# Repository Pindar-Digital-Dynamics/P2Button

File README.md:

# P2Button
The Pbutton project is designed to create a Bluetooth Low Energy (BLE) controlled video recording system specifically for Android platforms, primarily for indoor environments like gyms. This innovative system enables users to operate video recording functions through a robust, mounted button system, making it highly accessible and user-friendly.

## Overview
This project is a BLE (Bluetooth Low Energy) device setup for the P2CAM application, featuring a combination of functionalities including:
- BLE services and characteristics for communication.
- An OLED display for visual feedback.
- A buzzer and LEDs for status indication.
- Button interactions for triggering specific actions.

The code is designed to manage device states, interact with a BLE client, and provide visual/audio feedback for user interactions.

---

## Features
1. **BLE Communication**:
   - Implements multiple services and characteristics.
   - Supports read, write, indicate, and notify operations.
   - Handles commands like "Unlock", "Record", "Upload", "Login", and more.

2. **OLED Display**:
   - Displays the P2CAM logo, messages, and countdown timers.
   - Provides visual feedback during various states.

3. **Device States**:
   - The device transitions through states such as `NOT_PAIRED`, `LOGGED_LOCKED`, `CAMERA_UNLOCKED`, `RECORDING`, and more.

4. **LED Indications**:
   - Different LED colors indicate different device states.

5. **Buzzer Notifications**:
   - Provides audio feedback for specific actions.

6. **Button Interaction**:
   - Short and long press interactions trigger state changes and actions.

---

## Hardware Requirements
- **Microcontroller**: ESP32 or similar with BLE support.
- **OLED Display**: 128x64 resolution (I2C interface).
- **LEDs**: Blue, Green, and Red LEDs.
- **Buzzer**: For audio notifications.
- **Push Buttons**: For user interactions.
- **Battery Monitoring Pin**: For battery level feedback.

---

## Software Requirements
- **Arduino IDE** with the following libraries:
  - [Adafruit GFX Library](https://github.com/adafruit/Adafruit-GFX-Library)
  - [Adafruit SSD1306 Library](https://github.com/adafruit/Adafruit_SSD1306)
  - [BLEDevice Library](https://github.com/nkolban/esp32-snippets)
  - Wire library (default in Arduino IDE)

---

## Pin Configuration
| Component       | Pin   |
|------------------|-------|
| Blue LED         | 9     |
| Green LED        | 10    |
| Red LED          | 20    |
| Buzzer           | 5     |
| Button           | 21    |
| Unpair Button    | 3     |
| Battery Monitor  | 34    |
| OLED SDA         | 6     |
| OLED SCL         | 7     |

---

## BLE Setup
### Services
1. **Service 1 (UUID: 19b10000-e8f2-537e-4f6c-d104768a1214)**
   - Unlock Button
   - Unlock
   - Record Button
   - Record
   - Upload Button

2. **Service 2 (UUID: 19b20000-e8f2-537e-4f6c-d104768a1214)**
   - Upload
   - Setup
   - Login
   - Logout
   - Sleep

### Commands
The following commands are supported via BLE:
- `Login`: Log into the device.
- `Unlock`: Transition to the camera unlocked state.
- `Record`: Start recording.
- `Upload`: Start uploading data.
- `Logout`: Log out from the device.
- `Sleep`: Transition to sleep mode.

---

## Setup and Usage
1. **Hardware Setup**:
   - Connect the components as per the pin configuration table.
   - Ensure the OLED display is properly connected via I2C.

2. **Software Setup**:
   - Install the required libraries in Arduino IDE.
   - Compile and upload the code to your ESP32.

3. **Operation**:
   - Power on the device.
   - Pair with the BLE client (e.g., smartphone app).
   - Use the buttons for various actions.
   - Observe the OLED, LED, and buzzer for feedback.

4. **Resetting**:
   - Use the unpair button to reset the BLE pairing.

---

## Additional Information
- **OLED Bitmap**: Displays the P2CAM logo at startup.
- **Timers**:
  - Button holds initiate a countdown before actions.
- **Error Handling**:
  - Logs errors like failed BLE characteristic creation to the serial monitor.

---

## Troubleshooting
- **OLED Not Working**:
  - Verify the I2C address (default is `0x3C`).
  - Check SDA and SCL pin connections.

- **BLE Issues**:
  - Ensure BLE is enabled on the client device.
  - Restart advertising if connection drops.

- **No Buzzer Sound**:
  - Check buzzer pin connection and voltage.

---

## License
...

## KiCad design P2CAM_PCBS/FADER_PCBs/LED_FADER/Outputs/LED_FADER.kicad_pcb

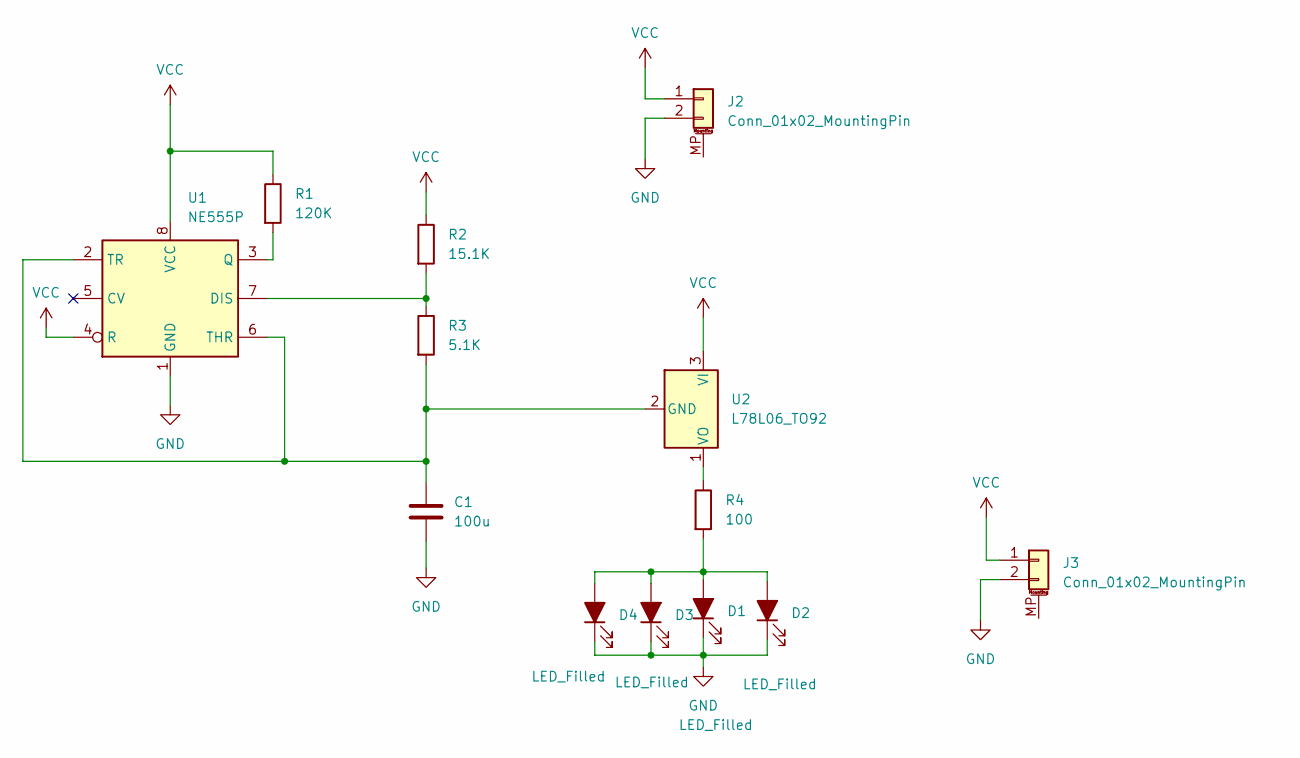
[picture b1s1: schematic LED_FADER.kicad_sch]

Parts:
C1: 100u; CP_Radial_D5.0mm_P2.50mm
D1, D2, D3, D4: LED_Filled; LED_D3.0mm
J2, J3: Conn_01x02_MountingPin; PinHeader_1x02_P2.54mm_Vertical
R1: 120K; R_Axial_DIN0207_L6.3mm_D2.5mm_P7.62mm_Horizontal
R2: 15.1K; R_Axial_DIN0207_L6.3mm_D2.5mm_P7.62mm_Horizontal
R3: 5.1K; R_Axial_DIN0207_L6.3mm_D2.5mm_P7.62mm_Horizontal
R4: 100; R_Axial_DIN0207_L6.3mm_D2.5mm_P7.62mm_Horizontal
U1: NE555P; DIP-8_W7.62mm
U2: L78L06_TO92; TO-92L_Inline

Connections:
GND: C1.2, D1.1 (K), D2.1 (K), D3.1 (K), D4.1 (K), J2.2, J3.2, U1.1 (GND)
unnamed: D1.2 (A), D2.2 (A), D3.2 (A), D4.2 (A), R4.2
unnamed: R2.2, R3.1, U1.7 (DIS)
unnamed: R1.2, U1.3 (Q)
unnamed: C1.1, R3.2, U1.2 (TR), U1.6 (THR), U2.2 (GND)
unnamed: R4.1, U2.1 (VO)
VCC: J2.1, J3.1, R1.1, R2.1, U1.4 (R), U1.8 (VCC), U2.3 (VI)

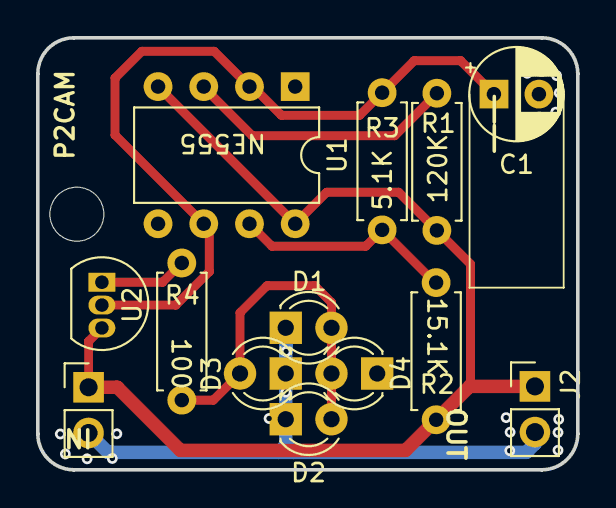
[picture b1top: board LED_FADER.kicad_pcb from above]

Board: 2 copper layers, 30.0 x 24.0 mm, 13 parts (0 on the bottom side), 7 nets.

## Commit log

2025-01-13 Create P2Button.ino
    add first one-file code of P2Button
2025-02-10 Add web app
2025-07-02 initial project
2025-07-02 add .git ignore
2025-08-11 Create README.md
    Add README for Xiao ESP32-S3 Plus project
2025-08-11 Create README.md
    Firmware folder added
2025-08-11 Add files via upload
    ".ino" file for new version button with new recording session added
2025-08-11 Add files via upload
    Create ui_header and move UI headers into it; update include paths
2025-08-14 Update ESP32_s3PLUS_NewRECORDING.ino
    The last version of Button
    - Added User guidance and ERRORs
    - Two Recording screens
2025-09-30 Create P2CAM_PCBs
    new Folder for all PCBs
2025-09-30 Create FADER_PCB
2025-09-30 Create Outputs
2025-09-30 Create READEME
2026-06-08 docs(ota): API specification for OTA + remote logging + anti-theft (T22)
    Locks the BLE wire format + module responsibilities for the v1.0 OTA system.
    This document is the contract between MoSaleh (backend/mobile) and Ali (firmware).
    Scope (Ali's 4 firmware modules):
    - firmware/ota.cpp — FIRMWARE_UPDATE_SERVICE + esp_ota_*
    - firmware/logger.cpp — SD_MMC ring buffer + LOGS_SERVICE
    - firmware/boot_validation.cpp — 30s health check + auto-rollback
2026-06-08 feat(ota): embed ECDSA P-256 firmware-signing public key (T22.3)
    v6 SUPER PLAN T22.3 — Ali will use this header in ota.cpp to verify firmware
    signatures with mbedtls_pk_parse_public_key() before opening the OTA partition.
    Format: SubjectPublicKeyInfo DER (RFC 5280), 91 bytes.
    Private key location: ~/.p2cam-secrets/p2button-signing.pem.gpg (MoSaleh Mac,
    GPG AES-256 encrypted). Workflow documented in firmware/include/signing_pubkey.h.
    Corresponds to mobile constant:
